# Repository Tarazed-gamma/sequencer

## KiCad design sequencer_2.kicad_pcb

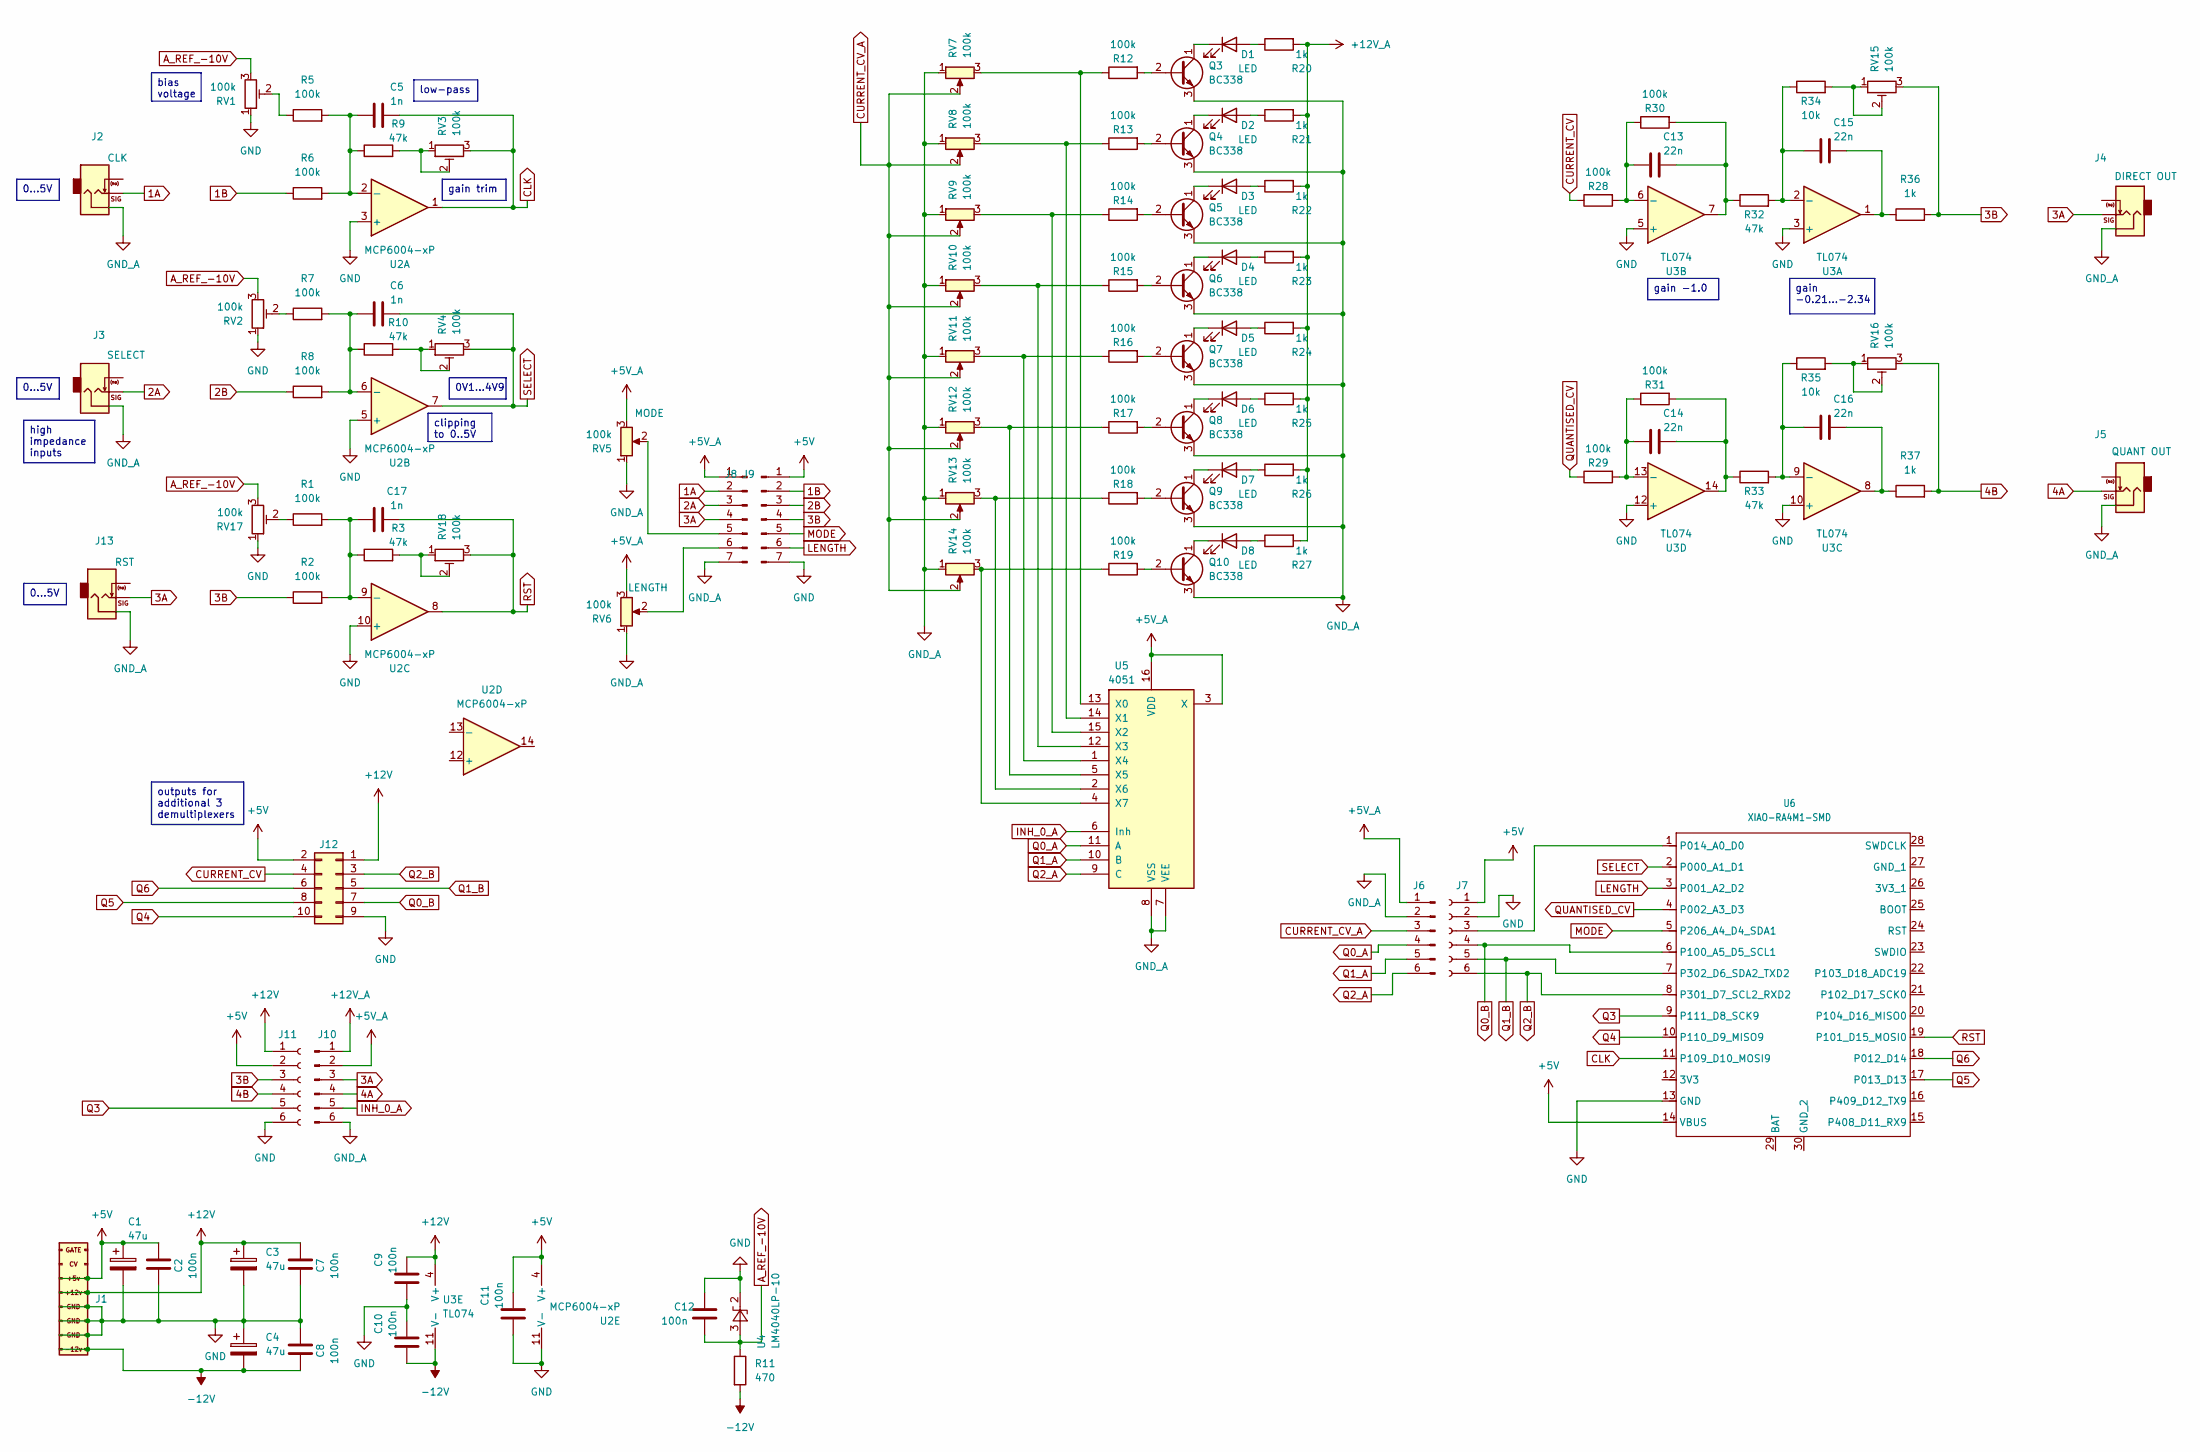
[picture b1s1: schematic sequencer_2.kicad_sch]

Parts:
C1, C3, C4: 47u; CP_Radial_D6.3mm_P2.50mm
C2, C7, C8, C9, C10, C11, C12: 100n; C_Rect_L7.0mm_W2.5mm_P5.00mm
C5, C6, C17: 1n; C_Disc_D3.4mm_W2.1mm_P2.50mm
C13, C14, C15, C16: 22n; C_Disc_D3.4mm_W2.1mm_P2.50mm
D1, D2, D3, D4, D5, D6, D7, D8: LED; LED_D5.0mm_Clear
J1: EuroPower16 THT; IDC-Header_2x08_P2.54mm_Vertical
J2, J3, J4, J5, J13: Jack_3.5mm_QingPu_WQP-PJ398SM_Vertical_CircularHoles
J6, J10: PinHeader_1x06_P2.54mm_Vertical
J7, J11: PinSocket_1x06_P2.54mm_Vertical
J8: PinHeader_1x07_P2.54mm_Vertical
J9: PinSocket_1x07_P2.54mm_Vertical
J12: PinSocket_2x05_P2.54mm_Vertical
Q3, Q4, Q5, Q6, Q7, Q8, Q9, Q10: BC338; TO-92_Inline_Wide
R1, R2, R5, R6, R7, R8, R12, R13, R14, R15, R16, R17, R18, R19, R28, R29, R30, R31: 100k; R_Axial_DIN0207_L6.3mm_D2.5mm_P7.62mm_Horizontal
R3, R9, R10, R32, R33: 47k; R_Axial_DIN0207_L6.3mm_D2.5mm_P7.62mm_Horizontal
R11: 470; R_Axial_DIN0207_L6.3mm_D2.5mm_P7.62mm_Horizontal
R20, R21, R22, R23, R24, R25, R26, R27, R36, R37: 1k; R_Axial_DIN0207_L6.3mm_D2.5mm_P7.62mm_Horizontal
R34, R35: 10k; R_Axial_DIN0207_L6.3mm_D2.5mm_P7.62mm_Horizontal
RV1, RV2, RV3, RV4, RV15, RV16, RV17, RV18: 100k; Potentiometer_Bourns_3296W_Vertical
RV5, RV6, RV7, RV8, RV9, RV10, RV11, RV12, RV13, RV14: 100k; Potentiometer_Alpha_RD901F-40-00D_Single_Vertical
U2: MCP6004-xP; DIP-14_W7.62mm_LongPads
U3: TL074; DIP-14_W7.62mm_LongPads
U4: LM4040LP-10; TO-92_Inline_Wide
U5: 4051; DIP-16_W7.62mm_LongPads
U6: XIAO-RA4M1-SMD; XIAO-R4-DIP

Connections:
1A: J2.T, J8.2
1B: J9.2, R6.1
2A: J3.T, J8.3
2B: J9.3, R8.1
3A: J4.T, J8.4, J10.3, J13.T
3B: J9.4, J11.3, R2.1, R36.2, RV15.3
4A: J5.T, J10.4
4B: J11.4, R37.2, RV16.3
+5V: C1.1, C2.2, C11.2, J1.11 (+5V), J1.12 (+5V), J7.1, J9.1, J11.2, J12.2, U2.4 (V+), U6.14 (VBUS)
+5V_A: J6.1, J8.1, J10.2, RV5.3, RV6.3, U5.3 (X), U5.16 (VDD)
+12V: C3.1, C7.2, C9.2, J1.9 (+12V), J1.10 (+12V), J11.1, J12.1, U3.4 (V+)
+12V_A: J10.1, R20.2, R21.2, R22.2, R23.2, R24.2, R25.2, R26.2, R27.2
-12V: C4.2, C8.1, C10.1, J1.1 (-12V), J1.2 (-12V), R11.2, U3.11 (V-)
A_REF_-10V: C12.2, R11.1, RV1.3, RV2.3, RV17.3, U4.3 (A)
CLK: C5.2, RV3.3, U2.1, U6.11 (P109_D10_MOSI9)
CURRENT_CV: J12.4, R28.1
CURRENT_CV_A: J6.3, RV7.2, RV8.2, RV9.2, RV10.2, RV11.2, RV12.2, RV13.2, RV14.2
CV: J1.13 (CV), J1.14 (CV)
GATE: J1.15 (GATE), J1.16 (GATE)
GND: C1.2, C2.1, C3.2, C4.1, C7.1, C8.2, C9.1, C10.2, C11.1, C12.1, J1.3 (GND), J1.4 (GND), J1.5 (GND), J1.6 (GND), J1.7 (GND), J1.8 (GND), J7.2, J9.7, J11.6, J12.9, RV1.1, RV2.1, RV17.1, U2.3 (+), U2.5 (+), U2.10 (+), U2.11 (V-), U3.3 (+), U3.5 (+), U3.10 (+), U3.12 (+), U4.2 (K), U6.13 (GND)
GND_A: J2.S, J3.S, J4.S, J5.S, J6.2, J8.7, J10.6, J13.S, Q3.3 (E), Q4.3 (E), Q5.3 (E), Q6.3 (E), Q7.3 (E), Q8.3 (E), Q9.3 (E), Q10.3 (E), RV5.1, RV6.1, RV7.1, RV8.1, RV9.1, RV10.1, RV11.1, RV12.1, RV13.1, RV14.1, U5.7 (VEE), U5.8 (VSS)
INH_0_A: J10.5, U5.6 (Inh)
LENGTH: J9.6, U6.3 (P001_A2_D2)
MODE: J9.5, U6.5 (P206_A4_D4_SDA1)
unnamed: C13.2, R30.2, R32.1, U3.7
unnamed: C14.2, R31.2, R33.1, U3.14
unnamed: C15.2, R36.1, U3.1
unnamed: C16.2, R37.1, U3.8
unnamed: D1.2 (A), R20.1
unnamed: D1.1 (K), Q3.1 (C)
unnamed: D2.2 (A), R21.1
unnamed: D2.1 (K), Q4.1 (C)
unnamed: D3.2 (A), R22.1
unnamed: D3.1 (K), Q5.1 (C)
unnamed: D4.2 (A), R23.1
unnamed: D4.1 (K), Q6.1 (C)
unnamed: D5.2 (A), R24.1
unnamed: D5.1 (K), Q7.1 (C)
unnamed: D6.2 (A), R25.1
unnamed: D6.1 (K), Q8.1 (C)
unnamed: D7.2 (A), R26.1
unnamed: D7.1 (K), Q9.1 (C)
unnamed: D8.2 (A), R27.1
unnamed: D8.1 (K), Q10.1 (C)
unnamed: J7.3, U6.1 (P014_A0_D0)
unnamed: J8.5, RV5.2
unnamed: J8.6, RV6.2
unnamed: Q3.2 (B), R12.2
unnamed: Q4.2 (B), R13.2
unnamed: Q5.2 (B), R14.2
unnamed: Q6.2 (B), R15.2
unnamed: Q7.2 (B), R16.2
unnamed: Q8.2 (B), R17.2
unnamed: Q9.2 (B), R18.2
unnamed: Q10.2 (B), R19.2
unnamed: R1.1, RV17.2
unnamed: R3.2, RV18.1, RV18.2
unnamed: R5.1, RV1.2
unnamed: R7.1, RV2.2
unnamed: R9.2, RV3.1, RV3.2
unnamed: R10.2, RV4.1, RV4.2
unnamed: R34.2, RV15.1, RV15.2
unnamed: R35.2, RV16.1, RV16.2
unnamed: C5.1, R5.2, R6.2, R9.1, U2.2 (-)
unnamed: C6.1, R7.2, R8.2, R10.1, U2.6 (-)
unnamed: C17.1, R1.2, R2.2, R3.1, U2.9 (-)
unnamed: C15.1, R32.2, R34.1, U3.2 (-)
unnamed: C13.1, R28.2, R30.1, U3.6 (-)
unnamed: C16.1, R33.2, R35.1, U3.9 (-)
unnamed: C14.1, R29.2, R31.1, U3.13 (-)
unnamed: R12.1, RV7.3, U5.13 (X0)
unnamed: R13.1, RV8.3, U5.14 (X1)
unnamed: R14.1, RV9.3, U5.15 (X2)
unnamed: R15.1, RV10.3, U5.12 (X3)
unnamed: R16.1, RV11.3, U5.1 (X4)
unnamed: R17.1, RV12.3, U5.5 (X5)
unnamed: R18.1, RV13.3, U5.2 (X6)
unnamed: R19.1, RV14.3, U5.4 (X7)
Q0_A: J6.4, U5.11 (A)
Q0_B: J7.4, J12.7, U6.6 (P100_A5_D5_SCL1)
Q1_A: J6.5, U5.10 (B)
Q1_B: J7.5, J12.5, U6.7 (P302_D6_SDA2_TXD2)
Q2_A: J6.6, U5.9 (C)
Q2_B: J7.6, J12.3, U6.8 (P301_D7_SCL2_RXD2)
Q3: J11.5, U6.9 (P111_D8_SCK9)
Q4: J12.10, U6.10 (P110_D9_MISO9)
Q5: J12.8, U6.17 (P013_D13)
Q6: J12.6, U6.18 (P012_D14)
QUANTISED_CV: R29.1, U6.4 (P002_A3_D3)
RST: C17.2, RV18.3, U2.8, U6.19 (P101_D15_MOSI0)
SELECT: C6.2, RV4.3, U2.7, U6.2 (P000_A1_D1)

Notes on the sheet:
0...5V
high impedance inputs
outputs for additional 3 demultiplexers
0V1...4V9
gain -0.21...-2.34
bias voltage
clipping to 0..5V
gain -1.0
low-pass
gain trim

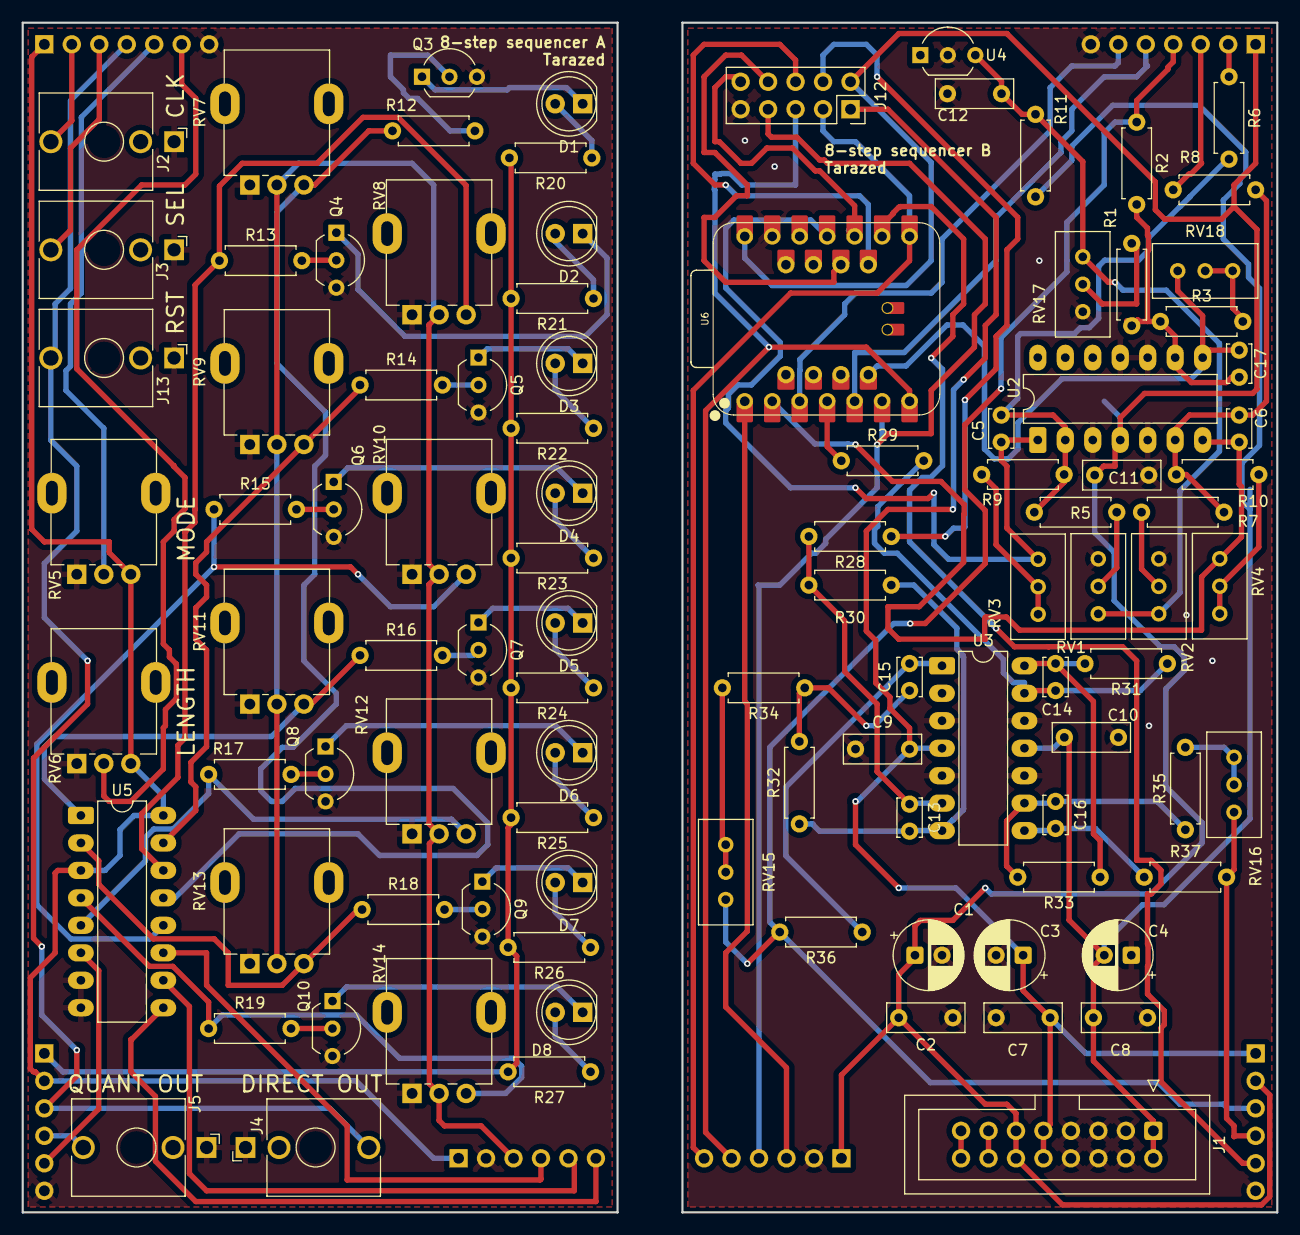
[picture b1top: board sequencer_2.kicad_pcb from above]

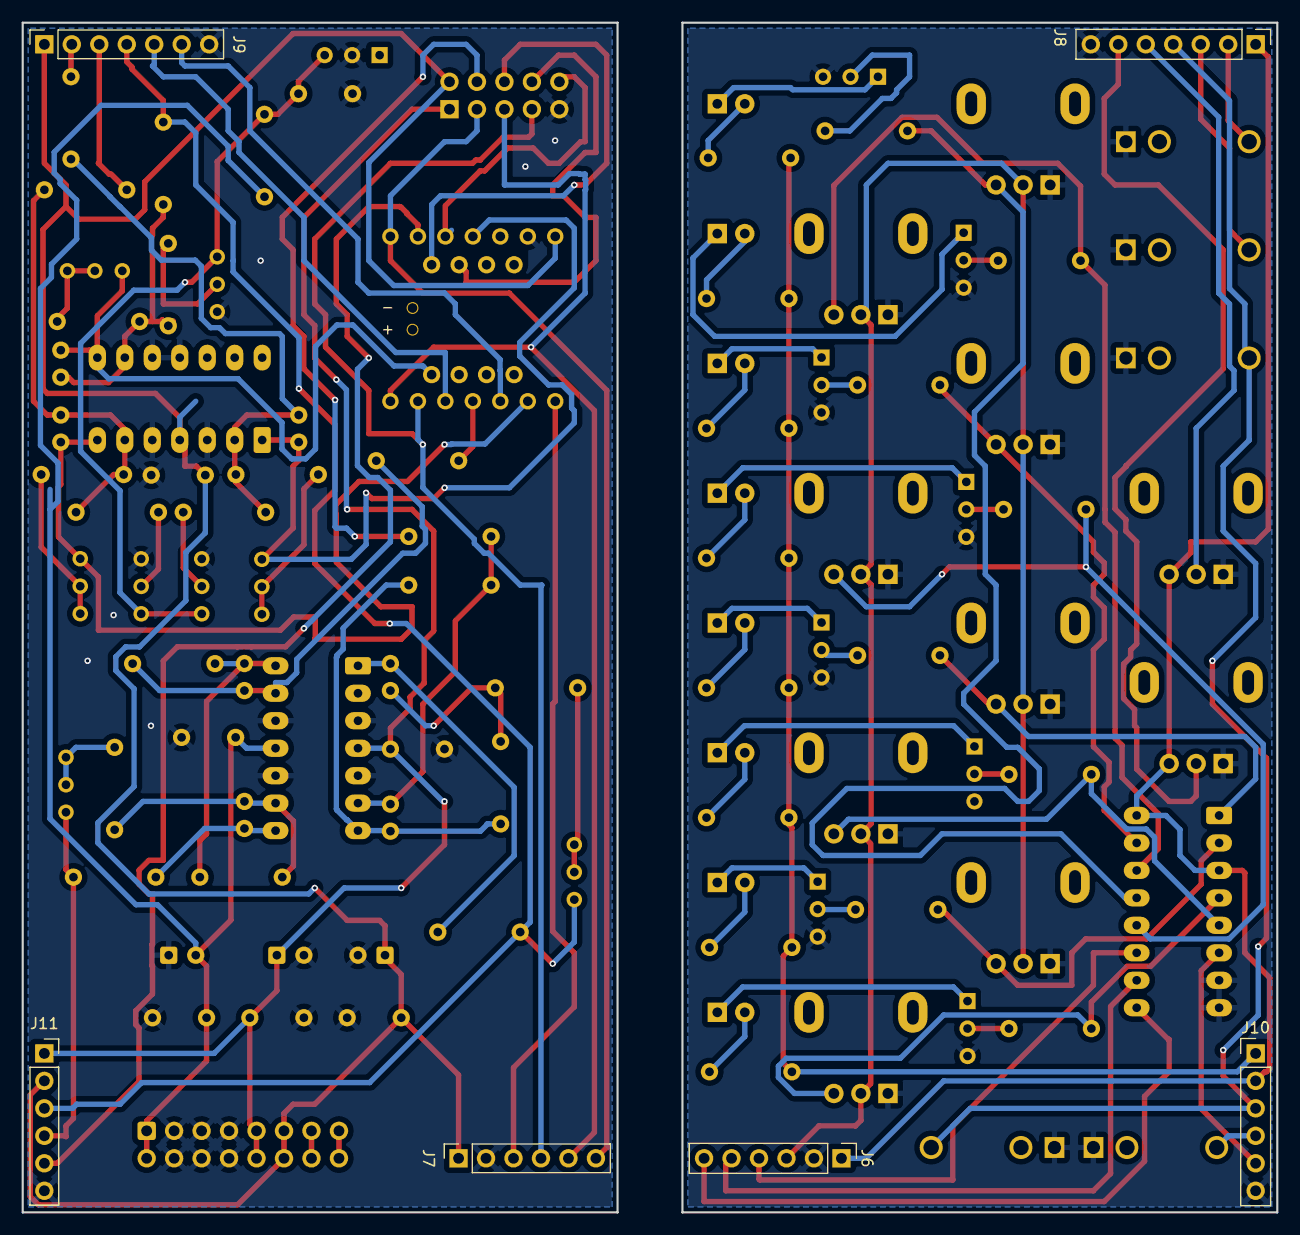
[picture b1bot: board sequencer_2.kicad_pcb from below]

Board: 2 copper layers, 116.0 x 110.0 mm, 105 parts (6 on the bottom side), 91 nets.

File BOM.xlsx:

Reference | Qty | Value | DNP | Footprint | Datasheet
C1,C3,C4 | 3 | 47u |  | Capacitor_THT:CP_Radial_D6.3mm_P2.50mm | ~
C2,C7,C8,C9,C10,C11,C12 | 7 | 100n |  | Capacitor_THT:C_Rect_L7.0mm_W2.5mm_P5.00mm | ~
C5,C6 | 2 | 1n |  | Capacitor_THT:C_Disc_D3.4mm_W2.1mm_P2.50mm | ~
C13,C14,C15,C16 | 4 | 22n |  | Capacitor_THT:C_Disc_D3.4mm_W2.1mm_P2.50mm | ~
D1,D2,D3,D4,D5,D6,D7,D8 | 8 | LED |  | LED_THT:LED_D5.0mm_Clear | ~
J1 | 1 | EuroPower16 THT |  | EuroRackTools:IDC-Header_2x08_P2.54mm_Vertical | ~
J2,J3,J4,J5 | 4 | ~ |  | EuroRackTools:Jack_3.5mm_QingPu_WQP-PJ398SM_Vertical_CircularHoles | ~
J6,J8,J10 | 3 | ~ |  | Connector_PinHeader_2.54mm:PinHeader_1x06_P2.54mm_Vertical | ~
J7,J9,J11 | 3 | ~ |  | Connector_PinSocket_2.54mm:PinSocket_1x06_P2.54mm_Vertical | ~
J12 | 1 | ~ |  | Connector_PinSocket_2.54mm:PinSocket_2x05_P2.54mm_Vertical | ~
Q3,Q4,Q5,Q6,Q7,Q8,Q9,Q10 | 8 | BC338 |  | Package_TO_SOT_THT:TO-92_Inline_Wide | http://diotec.com/tl_files/diotec/files/pdf/datasheets/bc337
R5,R6,R7,R8,R12,R13,R14,R15,R16,R17,R18,R19,R28,R29,R30,R31 | 16 | 100k |  | Resistor_THT:R_Axial_DIN0207_L6.3mm_D2.5mm_P7.62mm_Horizontal | ~
R9,R10,R32,R33 | 4 | 47k |  | Resistor_THT:R_Axial_DIN0207_L6.3mm_D2.5mm_P7.62mm_Horizontal | ~
R11 | 1 | 470 |  | Resistor_THT:R_Axial_DIN0207_L6.3mm_D2.5mm_P7.62mm_Horizontal | ~
R20,R21,R22,R23,R24,R25,R26,R27,R36,R37 | 10 | 1k |  | Resistor_THT:R_Axial_DIN0207_L6.3mm_D2.5mm_P7.62mm_Horizontal | ~
R34,R35 | 2 | 10k |  | Resistor_THT:R_Axial_DIN0207_L6.3mm_D2.5mm_P7.62mm_Horizontal | ~
RV1,RV2,RV3,RV4,RV15,RV16 | 6 | 100k |  | Potentiometer_THT:Potentiometer_Bourns_3296W_Vertical | ~
RV5,RV6,RV7,RV8,RV9,RV10,RV11,RV12,RV13,RV14 | 10 | 100k |  | EuroRackTools:Potentiometer_Alpha_RD901F-40-00D_Single_Vertical | ~
U2 | 1 | MCP6002-xP |  | Package_DIP:DIP-8_W7.62mm_LongPads | http://ww1.microchip.com/downloads/en/DeviceDoc/21733j.pdf
U3 | 1 | TL074 |  | Package_DIP:DIP-14_W7.62mm_LongPads | http://www.ti.com/lit/ds/symlink/tl071.pdf
U4 | 1 | LM4040LP-10 |  | Package_TO_SOT_THT:TO-92_Inline_Wide | http://www.ti.com/lit/ds/symlink/lm4040-n.pdf
U5 | 1 | 4051 |  | Package_DIP:DIP-16_W7.62mm_LongPads | http://www.intersil.com/content/dam/Intersil/documents/cd40/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
U6 | 1 | XIAO-RA4M1-SMD |  | XIAO_Series_Footprints:XIAO-R4-DIP

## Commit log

2026-03-08 Initial commit.
2026-03-11 J9 and J12 rework.
2026-03-11 RST input.
